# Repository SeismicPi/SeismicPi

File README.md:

# SeismicPi
4-Channel analog input board and standalone datalogger for Raspberry Pi

## Driver Installation
### Windows
- Plug in the SeismicPi to the computer. Windows will try and fail to install the driver.
- Download https://github.com/SeismicPi/SeismicPi/blob/master/Firmware/SeismicPi_Firmware/Documentation/cdc.inf.
- Open Device Manager, locate the SeismicPi device (usually under Ports, but possibly under Other Devices), right click and select Update Driver...
- Click Browse My Computer For Driver Software, then browse to the folder containing the cdc.inf you downloaded, and click Next.
- You may be asked to confirm the installation as the driver is unsigned, but click Continue Anyway.
- The driver should successfully install, and a COM port number should be assigned.

### Linux / Mac
- No driver is required - the SeismicPi should work as soon as you plug it in.

## COM Port Name
### Windows
Open Device Manager and locate the SeismicPi under the Ports category. The serial port name will be something like COMx where x is a number.

### Raspberry Pi
If the SeismicPi is connected to the GPIO port of the Raspberry Pi, use the serial port /dev/ttyAMA0. Otherwise, see the Linux instructions below.

### Linux / Mac
Run ls /dev at a terminal. The SeismicPi will have a name like /dev/ttyACMx, where x is a number.

## Required libraries
pyserial is required for the library to access the computer's serial port.
PyQt4 and pyQtGraph are also required only to run the demo applications and the settings GUI.
Platform-specific installation instructions for these libraries can be found on their respective websites. 

## Licensing

All code is provided under the MIT license (provided) unless listed here:
 - MCUOnEclipse USB-CDC Processor Expert Component, own license visible at https://github.com/ErichStyger/mcuoneclipse/blob/master/LICENSE.txt (https://github.com/ErichStyger/mcuoneclipse)
 - Arduino SD library, GNU-GPL license (https://github.com/arduino/Arduino/tree/master/libraries/SD)
 
All documentation and diagrams are provided under the Creative Commons Attribution-ShareAlike 4.0 license, https://creativecommons.org/licenses/by-sa/4.0/
 
All text and diagrams in iPython Notebooks are provided under the Creative Commons Attribution-ShareAlike 4.0 license, but any code examples contained within are provided under the MIT license.

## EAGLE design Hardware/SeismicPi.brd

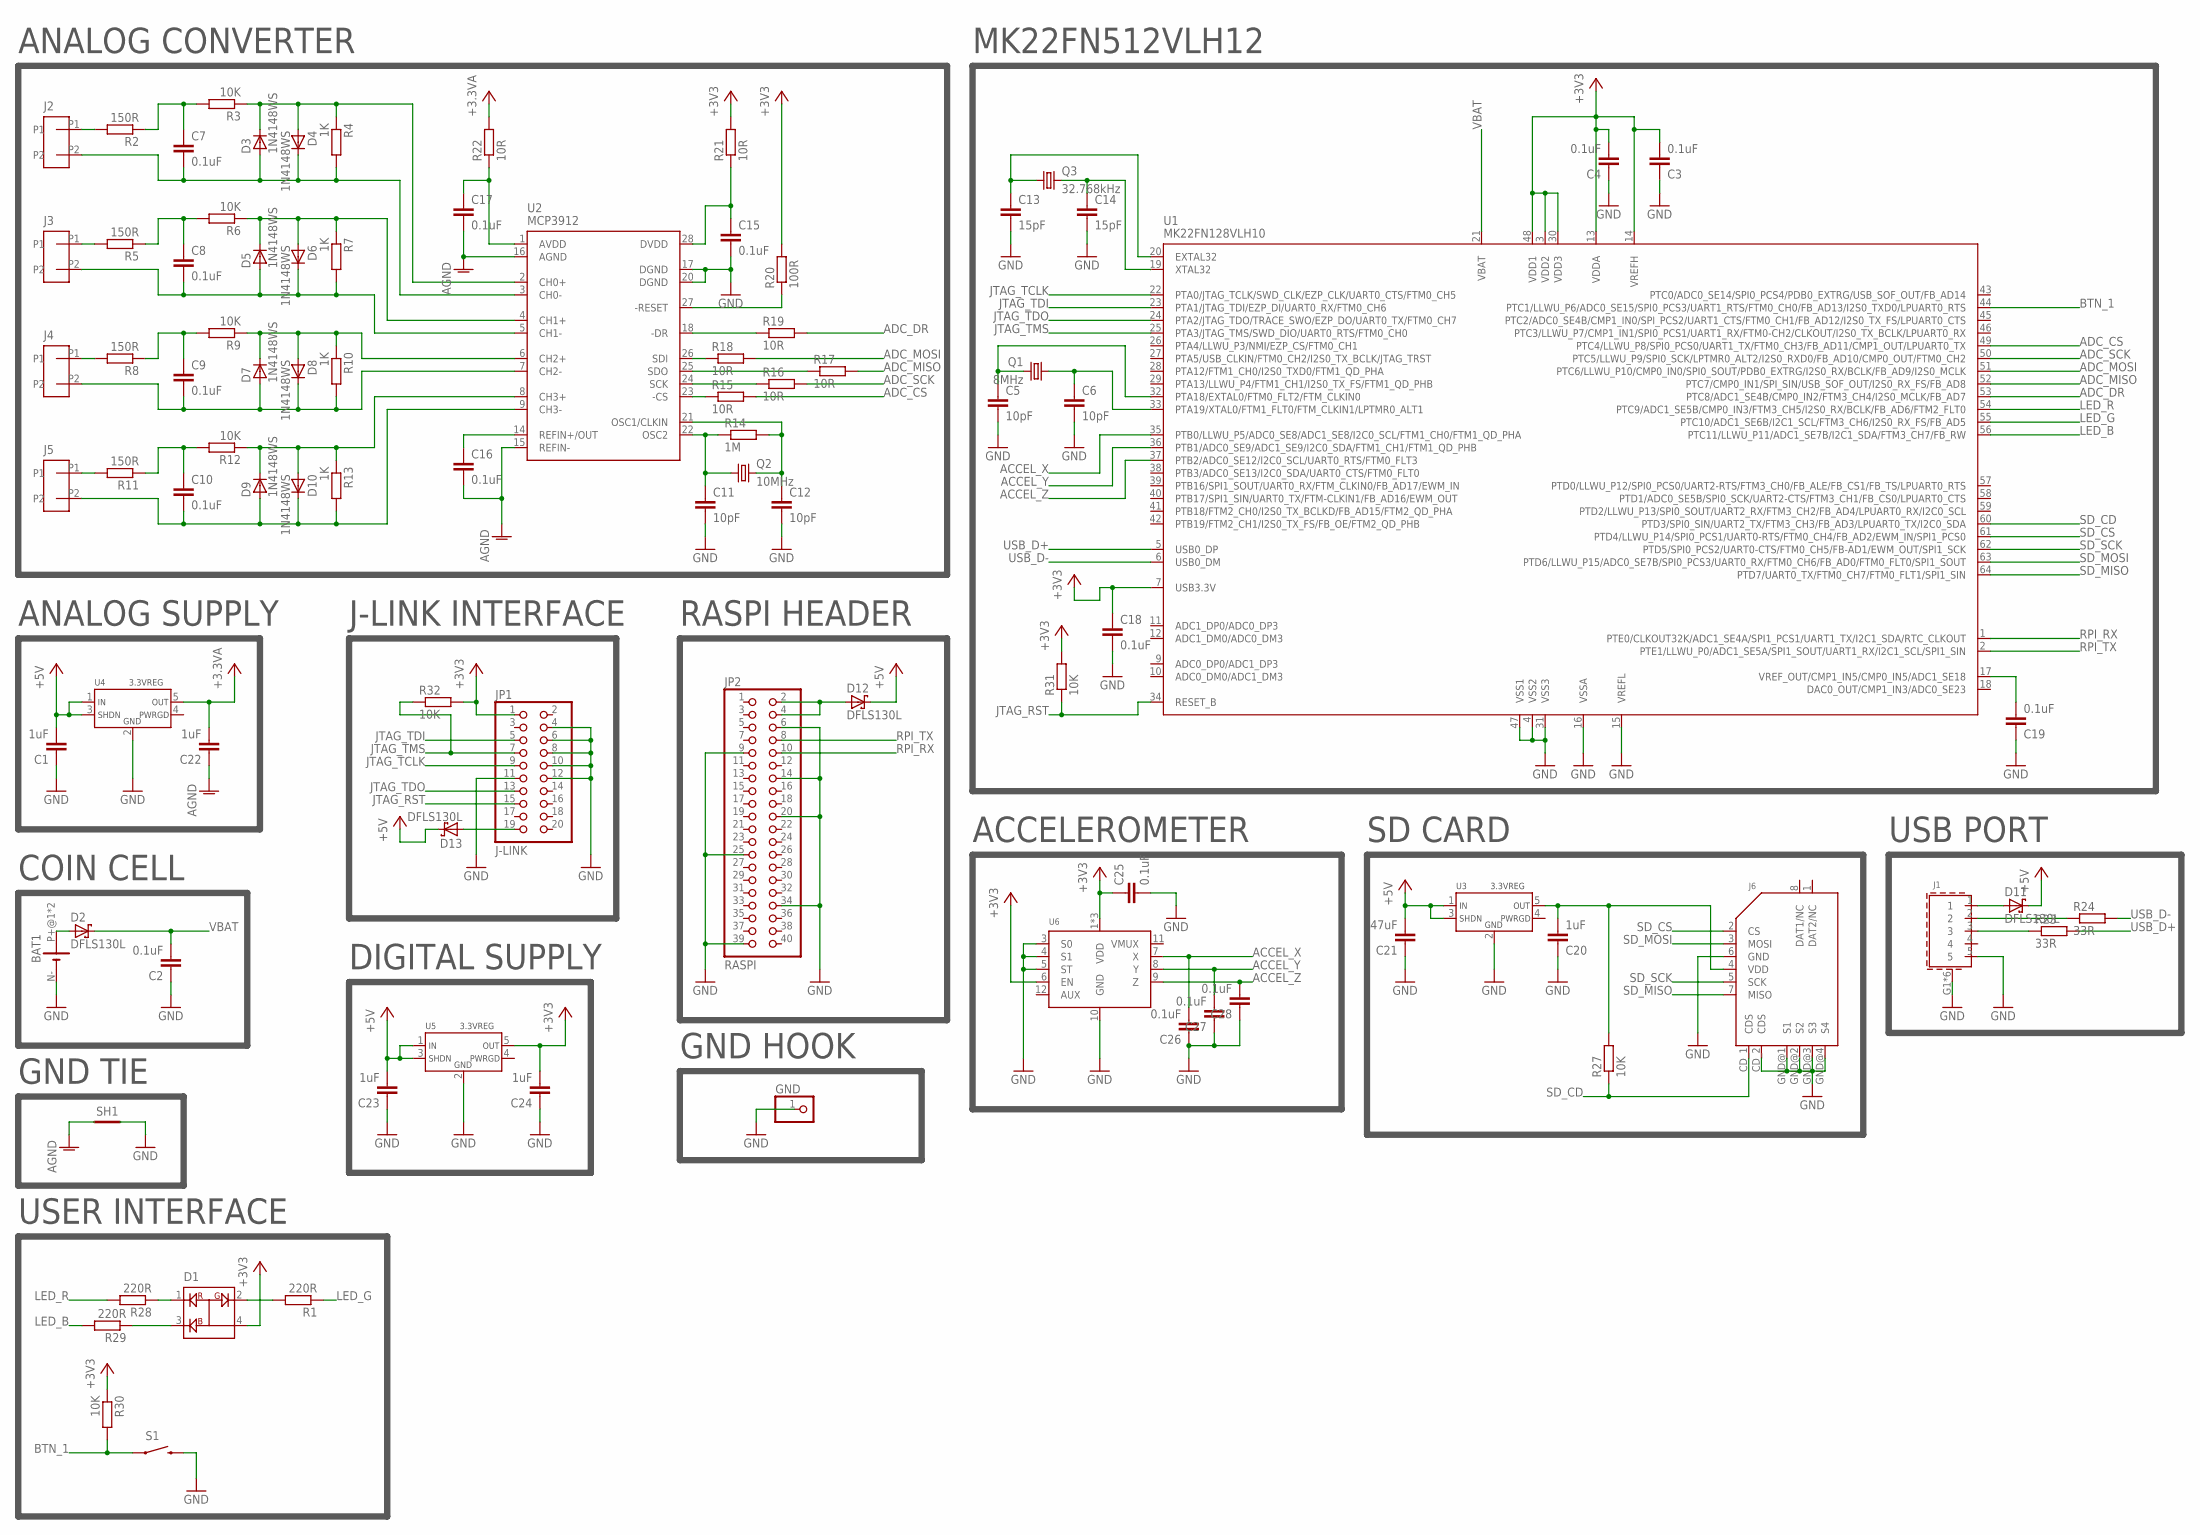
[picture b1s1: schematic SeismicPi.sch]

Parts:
BAT1: BATTERY-HOLDER_11.6MM; CELL_RETAINER_11.6MM
C1, C20, C22, C23, C24: 1uF; C2012
C2, C3, C4, C7, C8, C9, C10, C15, C16, C17, C18, C19, C25, C26, C27, C28: 0.1uF; C2012
C5, C6, C11, C12: 10pF; C2012
C13, C14: 15pF; C2012
C21: 47uF; C2012
D1: RGB-LED; P-LCC4-0
D2, D11, D12, D13: DFLS130L; POWERDI323
D3, D4, D5, D6, D7, D8, D9, D10: 1N4148WS; SOD323
GND: PINHD-1X1; 1X01
J1: USB-CONNMICRO; MICRO-USB
J2, J3, J4, J5: 2WAY-TERMINAL; 2WAY-5.08
J6: MICRO-SD
JP1: J-LINK; 2X10
JP2: RASPI; 2X20
Q1: 8MHz; ABM3B
Q2: 10MHz; ABM3B
Q3: 32.768kHz; MM20SS
R1, R28, R29: 220R; M2012
R2, R5, R8, R11: 150R; M2012
R3, R6, R9, R12, R27, R30, R31, R32: 10K; M2012
R4, R7, R10, R13: 1K; M2012
R14: 1M; M2012
R15, R16, R17, R18, R19, R21, R22: 10R; M2012
R20: 100R; M2012
R23, R24: 33R; M2012
S1: SWITCH-MOMENTARY-2PTH; TACTILE-PTH
SH1: SHORT-HT5; SHORT_TOP-50
U1: MK22FN128VLH10; LQFP-64_10X10X1.6
U2: MCP3912; SSOP28
U3, U4, U5: 3.3VREG; SOT23-5
U6: KXRB5-2050; LGA-14

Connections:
+3V3: C3.2, C4.2, C18.1, C24.2, C25.1, D1.4 (AN), JP1.1, R20.2, R21.2, R30.1, R31.2, R32.2, U1.3 (VDD2), U1.7 (USB3.3V), U1.13 (VDDA), U1.14 (VREFH), U1.30 (VDD3), U1.48 (VDD1), U5.5 (OUT), U6.1 (VDD), U6.6 (EN), U6.13 (VDD), U6.14 (VDD)
+3V3A: C22.2, R22.2, U4.5 (OUT)
+5V: C1.2, C21.2, C23.2, D11.C, D12.C, D13.C, U3.1 (IN), U3.3 (SHDN), U4.1 (IN), U4.3 (SHDN), U5.1 (IN), U5.3 (SHDN)
ACCEL_X: C26.2, U1.35 (PTB0/LLWU_P5/ADC0_SE8/ADC1_SE8/I2C0_SCL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), U6.7 (X)
ACCEL_Y: C27.2, U1.36 (PTB1/ADC0_SE9/ADC1_SE9/I2C0_SDA/FTM1_CH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), U6.8 (Y)
ACCEL_Z: C28.2, U1.37 (PTB2/ADC0_SE12/I2C0_SCL/UART0_RTS/FTM0_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), U6.9 (Z)
ADC_CS: R15.2, U1.49 (PTC4/LLWU_P8/SPI0_PCS0/UART1_TX/FTM0_CH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)
ADC_DR: R19.2, U1.53 (PTC8/ADC1_SE4B/CMP0_IN2/FTM3_CH4/I2S0_M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)
ADC_MISO: R17.2, U1.52 (PTC7/CMP0_IN1/SPI_SIN/USB_SOF_OUT/I2S0_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)
ADC_MOSI: R18.2, U1.51 (PTC6/LLWU_P10/CMP0_IN0/SPI0_SOUT/PDB0_E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)
ADC_SCK: R16.2, U1.50 (PTC5/LLWU_P9/SPI0_SCK/LPTMR0_ALT2/I2S0_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)
AGND: C16.2, C17.2, C22.1, SH1.1, U2.15 (REFIN-), U2.16 (AGND)
BTN_1: R30.2, S1.1, U1.44 (PTC1/LLWU_P6/ADC0_SE15/SPI0_PCS3/UART1_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)
GND: BAT1.N- (-), C1.1, C2.1, C3.1, C4.1, C5.2, C6.2, C11.2, C12.2, C13.2, C14.2, C15.2, C18.2, C19.1, C20.1, C21.1, C23.1, C24.1, C25.2, C26.1, C27.1, C28.1, GND.1, J1.5, J1.G1 (GND), J1.G2 (GND), J1.G3 (GND), J1.G4 (GND), J1.G5 (GND), J1.G6 (GND), J6.6 (GND), J6.CD_2 (CDS), J6.GND@1 (S1), J6.GND@2 (S2), J6.GND@3 (S3), J6.GND@4 (S4), JP1.4, JP1.6, JP1.8, JP1.10, JP1.11, JP1.12, JP2.6, JP2.9, JP2.14, JP2.20, JP2.25, JP2.34, JP2.39, S1.3 (2), SH1.2, U1.4 (VSS2), U1.15 (VREFL), U1.16 (VSSA), U1.31 (VSS3), U1.47 (VSS1), U2.17 (DGND), U2.20 (DGND), U3.2 (GND), U4.2 (GND), U5.2 (GND), U6.3 (S0), U6.4 (S1), U6.5 (ST), U6.10 (GND)
JTAG_RST: JP1.15, R31.1, U1.34 (RESET_B)
JTAG_TCLK: JP1.9, U1.22 (PTA0/JTAG_TCLK/SWD_CLK/EZP_CLK/UART0_CT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)
JTAG_TDI: JP1.5, U1.23 (PTA1/JTAG_TDI/EZP_DI/UART0_RX/FTM0_CH6)
JTAG_TDO: JP1.13, U1.24 (PTA2/JTAG_TDO/TRACE_SWO/EZP_DO/UART0_TX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)
JTAG_TMS: JP1.7, R32.1, U1.25 (PTA3/JTAG_TMS/SWD_DIO/UART0_RTS/FTM0_CH0)
LED_B: R29.2, U1.56 (PTC11/LLWU_P11/ADC1_SE7B/I2C1_SDA/FTM3_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)
LED_G: R1.1, U1.55 (PTC10/ADC1_SE6B/I2C1_SCL/FTM3_CH6/I2S0_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)
LED_R: R28.2, U1.54 (PTC9/ADC1_SE5B/CMP0_IN3/FTM3_CH5/I2S0_R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)
unnamed: D11.A, J1.1
unnamed: BAT1.P+@1 (+), BAT1.P+@2 (+), D2.A
unnamed: J2.P1, R2.2
unnamed: C5.1, Q1.3 (2), U1.32 (PTA18/EXTAL0/FTM0_FLT2/FTM_CLKIN0)
unnamed: C6.1, Q1.1, U1.33 (PTA19/XTAL0/FTM1_FLT0/FTM_CLKIN1/LPTMR0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)
unnamed: D3.1 (C), D4.2 (A), R3.1, R4.1, U2.2 (CH0+)
unnamed: C7.2, D3.2 (A), D4.1 (C), J2.P2, R4.2, U2.3 (CH0-)
unnamed: C12.1, Q2.3 (2), R14.2, U2.21 (OSC1/CLKIN)
unnamed: J3.P1, R5.2
unnamed: C13.1, Q3.1, U1.20 (EXTAL32)
unnamed: C14.1, Q3.4 (2), U1.19 (XTAL32)
unnamed: C7.1, R2.1, R3.2
unnamed: D5.1 (C), D6.2 (A), R6.1, R7.1, U2.4 (CH1+)
unnamed: C8.2, D5.2 (A), D6.1 (C), J3.P2, R7.2, U2.5 (CH1-)
unnamed: C8.1, R5.1, R6.2
unnamed: J4.P1, R8.2
unnamed: D7.1 (C), D8.2 (A), R9.1, R10.1, U2.6 (CH2+)
unnamed: C9.2, D7.2 (A), D8.1 (C), J4.P2, R10.2, U2.7 (CH2-)
unnamed: C9.1, R8.1, R9.2
unnamed: J5.P1, R11.2
unnamed: D9.1 (C), D10.2 (A), R12.1, R13.1, U2.8 (CH3+)
unnamed: C10.2, D9.2 (A), D10.1 (C), J5.P2, R13.2, U2.9 (CH3-)
unnamed: C10.1, R11.1, R12.2
unnamed: C11.1, Q2.1, R14.1, U2.22 (OSC2)
unnamed: C16.1, U2.14 (REFIN+/OUT)
unnamed: R20.1, U2.27 (-RESET)
unnamed: C17.1, R22.1, U2.1 (AVDD)
unnamed: R19.1, U2.18 (-DR)
unnamed: R18.1, U2.26 (SDI)
unnamed: R17.1, U2.25 (SDO)
unnamed: R16.1, U2.24 (SCK)
unnamed: R15.1, U2.23 (-CS)
unnamed: C19.2, U1.17 (VREF_OUT/CMP1_IN5/CMP0_IN5/ADC1_SE18)
unnamed: D12.A, JP2.2, JP2.4
unnamed: D1.1 (R), R28.1
unnamed: D1.3 (B), R29.1
unnamed: D1.2 (G), R1.2
unnamed: C15.1, R21.1, U2.28 (DVDD)
unnamed: J1.2, R24.1
unnamed: J1.3, R23.1
unnamed: D13.A, JP1.19
unnamed: C20.2, J6.4 (VDD), R27.2, U3.5 (OUT)
RPI_RX: JP2.10, U1.1 (PTE0/CLKOUT32K/ADC1_SE4A/SPI1_PCS1/UART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)
RPI_TX: JP2.8, U1.2 (PTE1/LLWU_P0/ADC1_SE5A/SPI1_SOUT/UART1_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)
SD_CD: J6.CD_1 (CDS), R27.1, U1.60 (PTD3/SPI0_SIN/UART2_TX/FTM3_CH3/FB_AD3/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)
SD_CS: J6.2 (CS), U1.61 (PTD4/LLWU_P14/SPI0_PCS1/UART0-RTS/FTM0_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)
SD_MISO: J6.7 (MISO), U1.64 (PTD7/UART0_TX/FTM0_CH7/FTM0_FLT1/SPI1_S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)
SD_MOSI: J6.3 (MOSI), U1.63 (PTD6/LLWU_P15/ADC0_SE7B/SPI0_PCS3/UART0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)
SD_SCK: J6.5 (SCK), U1.62 (PTD5/SPI0_PCS2/UART0-CTS/FTM0_CH5/FB-AD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)
USB_D+: R23.2, U1.5 (USB0_DP)
USB_D-: R24.2, U1.6 (USB0_DM)
VBAT: C2.2, D2.C, U1.21 (VBAT)

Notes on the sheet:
ANALOG CONVERTER
SD CARD
ANALOG SUPPLY
USER INTERFACE
COIN CELL
USB PORT
MK22FN512VLH12
J-LINK INTERFACE
RASPI HEADER
DIGITAL SUPPLY
GND TIE
GND HOOK
ACCELEROMETER

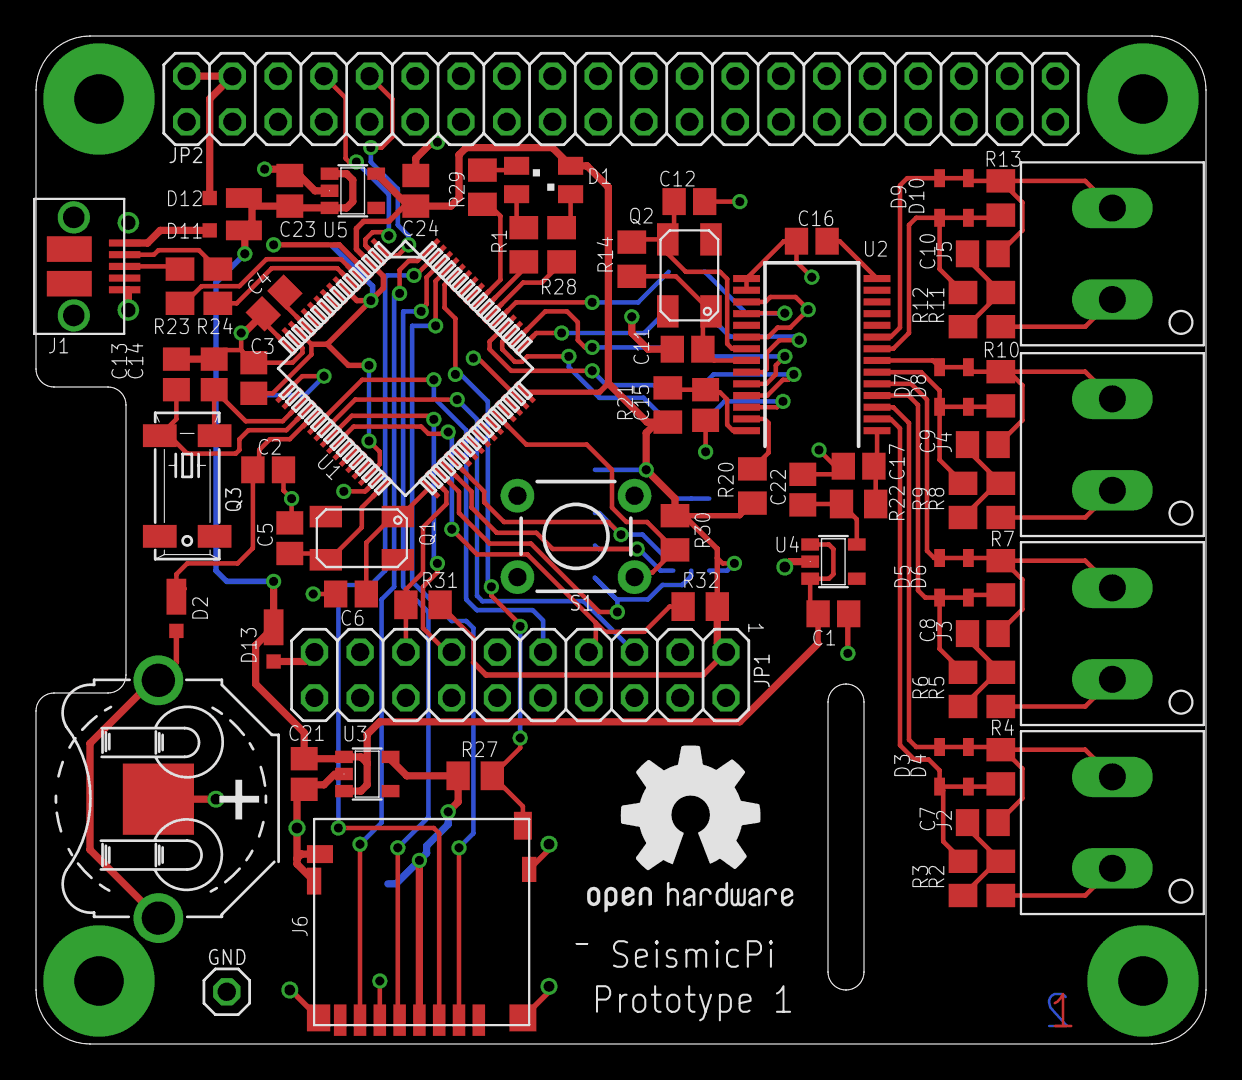
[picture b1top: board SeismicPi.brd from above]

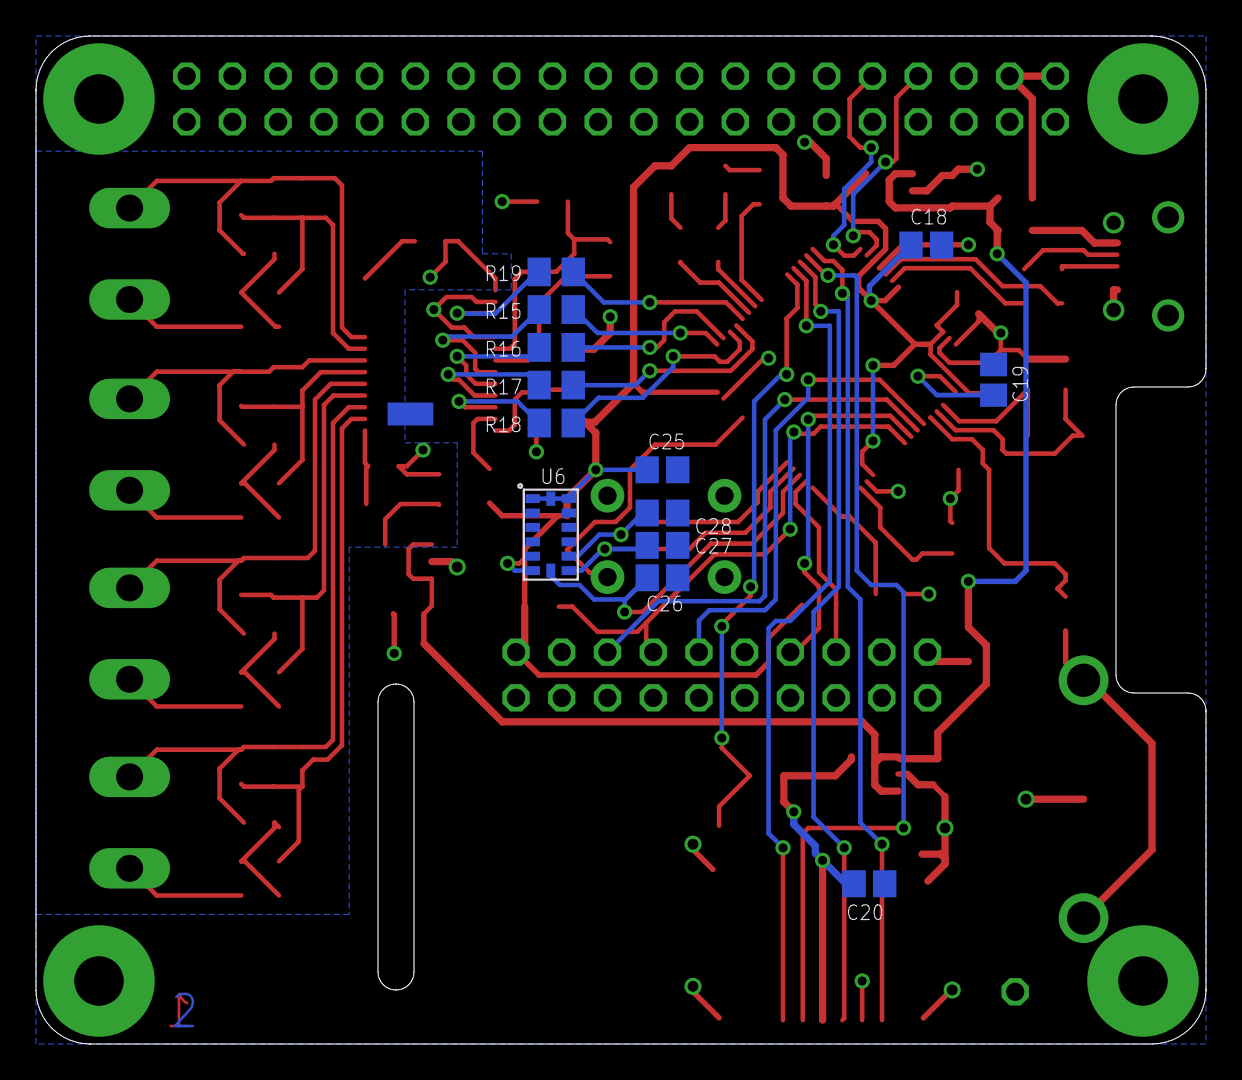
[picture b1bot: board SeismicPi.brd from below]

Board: 2 copper layers, 65.0 x 56.0 mm, 93 parts (14 on the bottom side), 74 nets.

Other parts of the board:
U$1: OSHW1

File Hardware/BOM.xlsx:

| Mouser
 | Name | Qty | Mouser P/N | Desc
 | U6 | 1 | 912-KXRB5-2050 | KXRB5 accelerometer
 | Farnell
 | Name | Qty | Farnell P/N | Desc
 | BAT1 | 1 pack (1) | 908642 | Keystone coin cell holder, pack of 5
 | C1, C20, C22, C23, C24 | 5 | 1759432 | 1uF 0805 ceramic capacitor
 | C2, C3, C4, C7, C8, C9, C10, C15, C16, C17, C18, C19, C25, C26, C27, C28 | 16 | 1759265 | 0.1uF 0805 ceramic capacitor
 | C5, C6, C11, C12 | 4 | 1759191 | 10pF 0805 ceramic capacitor
 | C13, C14 | 2 | 1759193 | 15pF 0805 ceramic capacitor
 | C21 | 1 | 2362109 | 47uF 0805 ceramic capacitor
 | D1 | 1 | 2401106 | RGB LED, PLCC package
 | D2, D11, D12, D13 | 4 | 1843673 | Recifier diode DFLS130L-7
 | D3, D4, D5, D6, D7, D8, D9, D10 | 8 | 1466524 | Signal diode 1N4148WS
 | GND | 1 pack (1) | 1701997 | Test pin, pack of 100
 | J1 | 1 | 2293752 | Micro-USB connector
 | J2, J3, J4, J5 | 4 | 2008019 | 2-way 5.08mm terminal block
 | J6 | 1 | 2293708 | Micro-SD socket
 | JP1 | 1 | 1593446 | 2x10 header
 | JP2 | 1 | 1569230 | 2x20 Stacking header socket
 | Q1 | 1 | 2467817 | 8MHz Crystal
 | Q2 | 1 | 2467799 | 10MHz Crystal
 | Q3 | 1 | 9713220 | 32.768kHz Crystal
 | R1, R28, R29 | 3 | 1469899 | 220R 0805 resistor
 | R2, R5, R8, R11 | 4 | 1469877 | 150R 0805 resistor
 | R3, R6, R9, R12, R27, R30, R31, R31 | 8 | 9237755 | 10K 0805 resistor
 | R4, R7, R10, R13 | 4 | 1099800 | 1K 0805 resistor
 | R14 | 1 | 2333577 | 1M 0805 resistor
 | R15, R16, R17, R18, R19, R21, R22 | 7 | 2333541 | 10R 0805 resistor
 | R20 | 1 | 2333586 | 100R resistor
 | R23, R24 | 2 | 2145508 | 33R resistor
 | S1 | 1 | 9471677 | Tactile button
 | U1 | 1 | 2434217 | MK22FN128VLH10 Freescale Kinetis SoC
 | U2 | 1 | 2460947 | MCP3912 Microchip analog front-end
 | U3, U4, U5 | 3 | 2361992 | 3.3v regulator

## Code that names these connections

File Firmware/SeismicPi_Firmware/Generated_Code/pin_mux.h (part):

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**                Custom name, Signal name                 : EXTAL32
**              Pin 21: VBAT                               : 
**                Custom name, Signal name                 : VBAT
**              Pin 22: PTA0/UART0_CTS_b/FTM0_CH5/JTAG_TCLK/SWD_CLK/EZP_CLK: 
**                Custom name, Signal name                 : J2_2/J11_1
**                Slew rate                                : <Automatic>
**                Open drain                               : <Automatic>
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**                Passive filter                           : <Automatic>
**                Pull select                              : <Automatic>
**                Pull enable                              : <Automatic>
**              Pin 23: PTA1/UART0_RX/FTM0_CH6/JTAG_TDI/EZP_DI: 
**                Custom name, Signal name                 : J1_8
**                Slew rate                                : <Automatic>
**                Open drain                               : <Automatic>
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**                Passive filter                           : <Automatic>
**                Pull select                              : <Automatic>
**                Pull enable                              : <Automatic>
**              Pin 24: PTA2/UART0_TX/FTM0_CH7/JTAG_TDO/TRACE_SWO/EZP_DO: 
**                Custom name, Signal name                 : J1_12
**                Slew rate                                : <Automatic>
**                Open drain                               : <Automatic>
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**                Passive filter                           : <Automatic>
**                Pull select                              : <Automatic>
**                Pull enable                              : <Automatic>
**              Pin 25: PTA3/UART0_RTS_b/FTM0_CH0/JTAG_TMS/SWD_DIO: 
**                Custom name, Signal name                 : J9_2/SWD_DIO_TGTMCU/J12_2
**                Slew rate                                : <Automatic>
**                Open drain                               : <Automatic>
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
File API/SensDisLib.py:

from pyqtgraph.Qt import QtGui, QtCore
import pyqtgraph as pg
from collections import deque
import threading
import time
import seismicpi


INPUT_CHANNEL_1 = 1
INPUT_CHANNEL_2 = 2
INPUT_CHANNEL_3 = 3
INPUT_CHANNEL_4 = 4
ACCEL_X = 5
ACCEL_Y = 6
ACCEL_Z = 7

SENSOR_DATA_BUFFER_LENGTH = 2000

class SensorChannel:
	def __init__(self, source, name=None):
		assert source >=1 and source <= 7, "Sensor source is invalid!"
		self.source = source
		self.name = name or "Channel %d" % (source)
		self.data = deque(maxlen=SENSOR_DATA_BUFFER_LENGTH)
		self.transform_function = lambda x: x
		self.plot = None
		if source >= ACCEL_X:
			self.set_range(0, 65536) # 16-bit accelerometer (unsigned)
		else:
			self.set_range(-8388608, 8388608) # 24-bit signed sensor input
	
	def _update_value(self, newVal):
		self.raw_value = newVal
		self.data.append(self.transform_function(newVal))
		
	def set_range(self, min_y, max_y):
		self.min_y = min_y
		self.max_y = max_y
		if self.plot:
			self.plot.setYRange(min_y, max_y)
	
	def set_transform_function(self, func):
		self.transform_function = lambda x: func(x)
	
	def set_name(self, name):
		self.name = name
		
	def get_raw_value(self):
		return self.raw_value
	
	def get_value(self):
		return self.transform_function(self.raw_value)


class SensorDisplay:
	
	def __init__(self, comport, displayTime = 2):
		global SENSOR_DATA_BUFFER_LENGTH
		#input is the maxDisplayTime in seconds
		self.numSensors = 0

		self.board = seismicpi.SeismicPi(comport)

		SENSOR_DATA_BUFFER_LENGTH = displayTime * 1000
		self.qx = deque(maxlen=SENSOR_DATA_BUFFER_LENGTH)

		self.app = QtGui.QApplication([])
		self.win = pg.GraphicsWindow(title = "Sensor Plots")
		self.win.resize(1000, 800)
		
		self.renderLock = False
		
		self.read_sensors = False
		self.read_accel = False
		
		self.pen_colors = ['r', 'g', 'b', 'y']
		
		self.sensors = []
		
		self.paused = False

		pg.setConfigOptions(antialias = False)

	def pause(self):
		self.paused = True
	
	def resume(self):
		self.paused = False
	
	def add(self, sensor):
		assert sensor, "Sensor is None!"
		if self.numSensors == 2:
			self.win.nextRow()
		
		plot = self.win.addPlot(title = sensor.name)
		plot.setYRange(sensor.min_y, sensor.max_y)
		self.sensors.append(sensor)
		sensor.plot = plot
		sensor.curve = plot.plot(pen=self.pen_colors[self.numSensors])
		if sensor.source >= ACCEL_X:
			self.read_accel = True
		else:
			self.read_sensors = True
		
		self.numSensors += 1
	
	def update(self):
		for sensor in self.sensors:
			if not self.renderLock:
				sensor.curve.setData(self.qx, sensor.data)

	def getNext(self):
		ptr = 0
		while True:
			time.sleep(.0001)
			if not self.paused:
				if self.read_sensors:
					self.sensor_values = self.board.get_sensor_values()
				if self.read_accel:
					self.accel_values = self.board.get_accel_values()
				self.renderLock = True
				for sensor in self.sensors:
					if sensor.source >= ACCEL_X:
						val = self.accel_values[sensor.source - ACCEL_X]
					else:
						val = self.sensor_values[sensor.source - INPUT_CHANNEL_1]
					sensor._update_value(val)
				self.qx.append(ptr)
				self.renderLock = False
				ptr+=1

	def runPlot(self):
		self.input_Thread = threading.Thread(target = self.getNext)
		self.input_Thread.daemon = True
		self.input_Thread.start()

		self.timer = QtCore.QTimer()
		self.timer.timeout.connect(self.update)
		self.timer.start()

		import sys
		if (sys.flags.interactive != 1) or not hasattr(QtCore, 'PYQT_VERSION'):
			QtGui.QApplication.instance().exec_()

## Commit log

2015-09-04 Added firmware projects
2015-09-04 Added Python API and demos
2015-09-04 Added Eagle board designs
2015-09-04 Added documentation
2015-09-04 Added lesson plans
2015-09-04 Updated license information
2015-09-05 Added binary converter script
2015-09-06 Improved raw binary converter
2015-09-06 Fixed readme
2015-09-22 Removed dependency on FileType
2015-09-22 Rewrote SensDisLib to support mixing accel and sensor inputs
2015-09-24 Removed dependency on Sensor
2015-09-25 Added XY-accelerometer plot demo
2015-09-28 Added BOM
2015-09-28 Added config.txt documentation

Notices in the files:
Firmware/SeismicPi_Firmware/Generated_Code/pin_mux.h:
Copyright : 1997 - 2015 Freescale Semiconductor, Inc.
All Rights Reserved.
parts and their libraries:
SparkFun-Electromechanical: Licensing: Creative Commons ShareAlike 4.0 International - https://creativecommons.org/licenses/by-sa/4.0
